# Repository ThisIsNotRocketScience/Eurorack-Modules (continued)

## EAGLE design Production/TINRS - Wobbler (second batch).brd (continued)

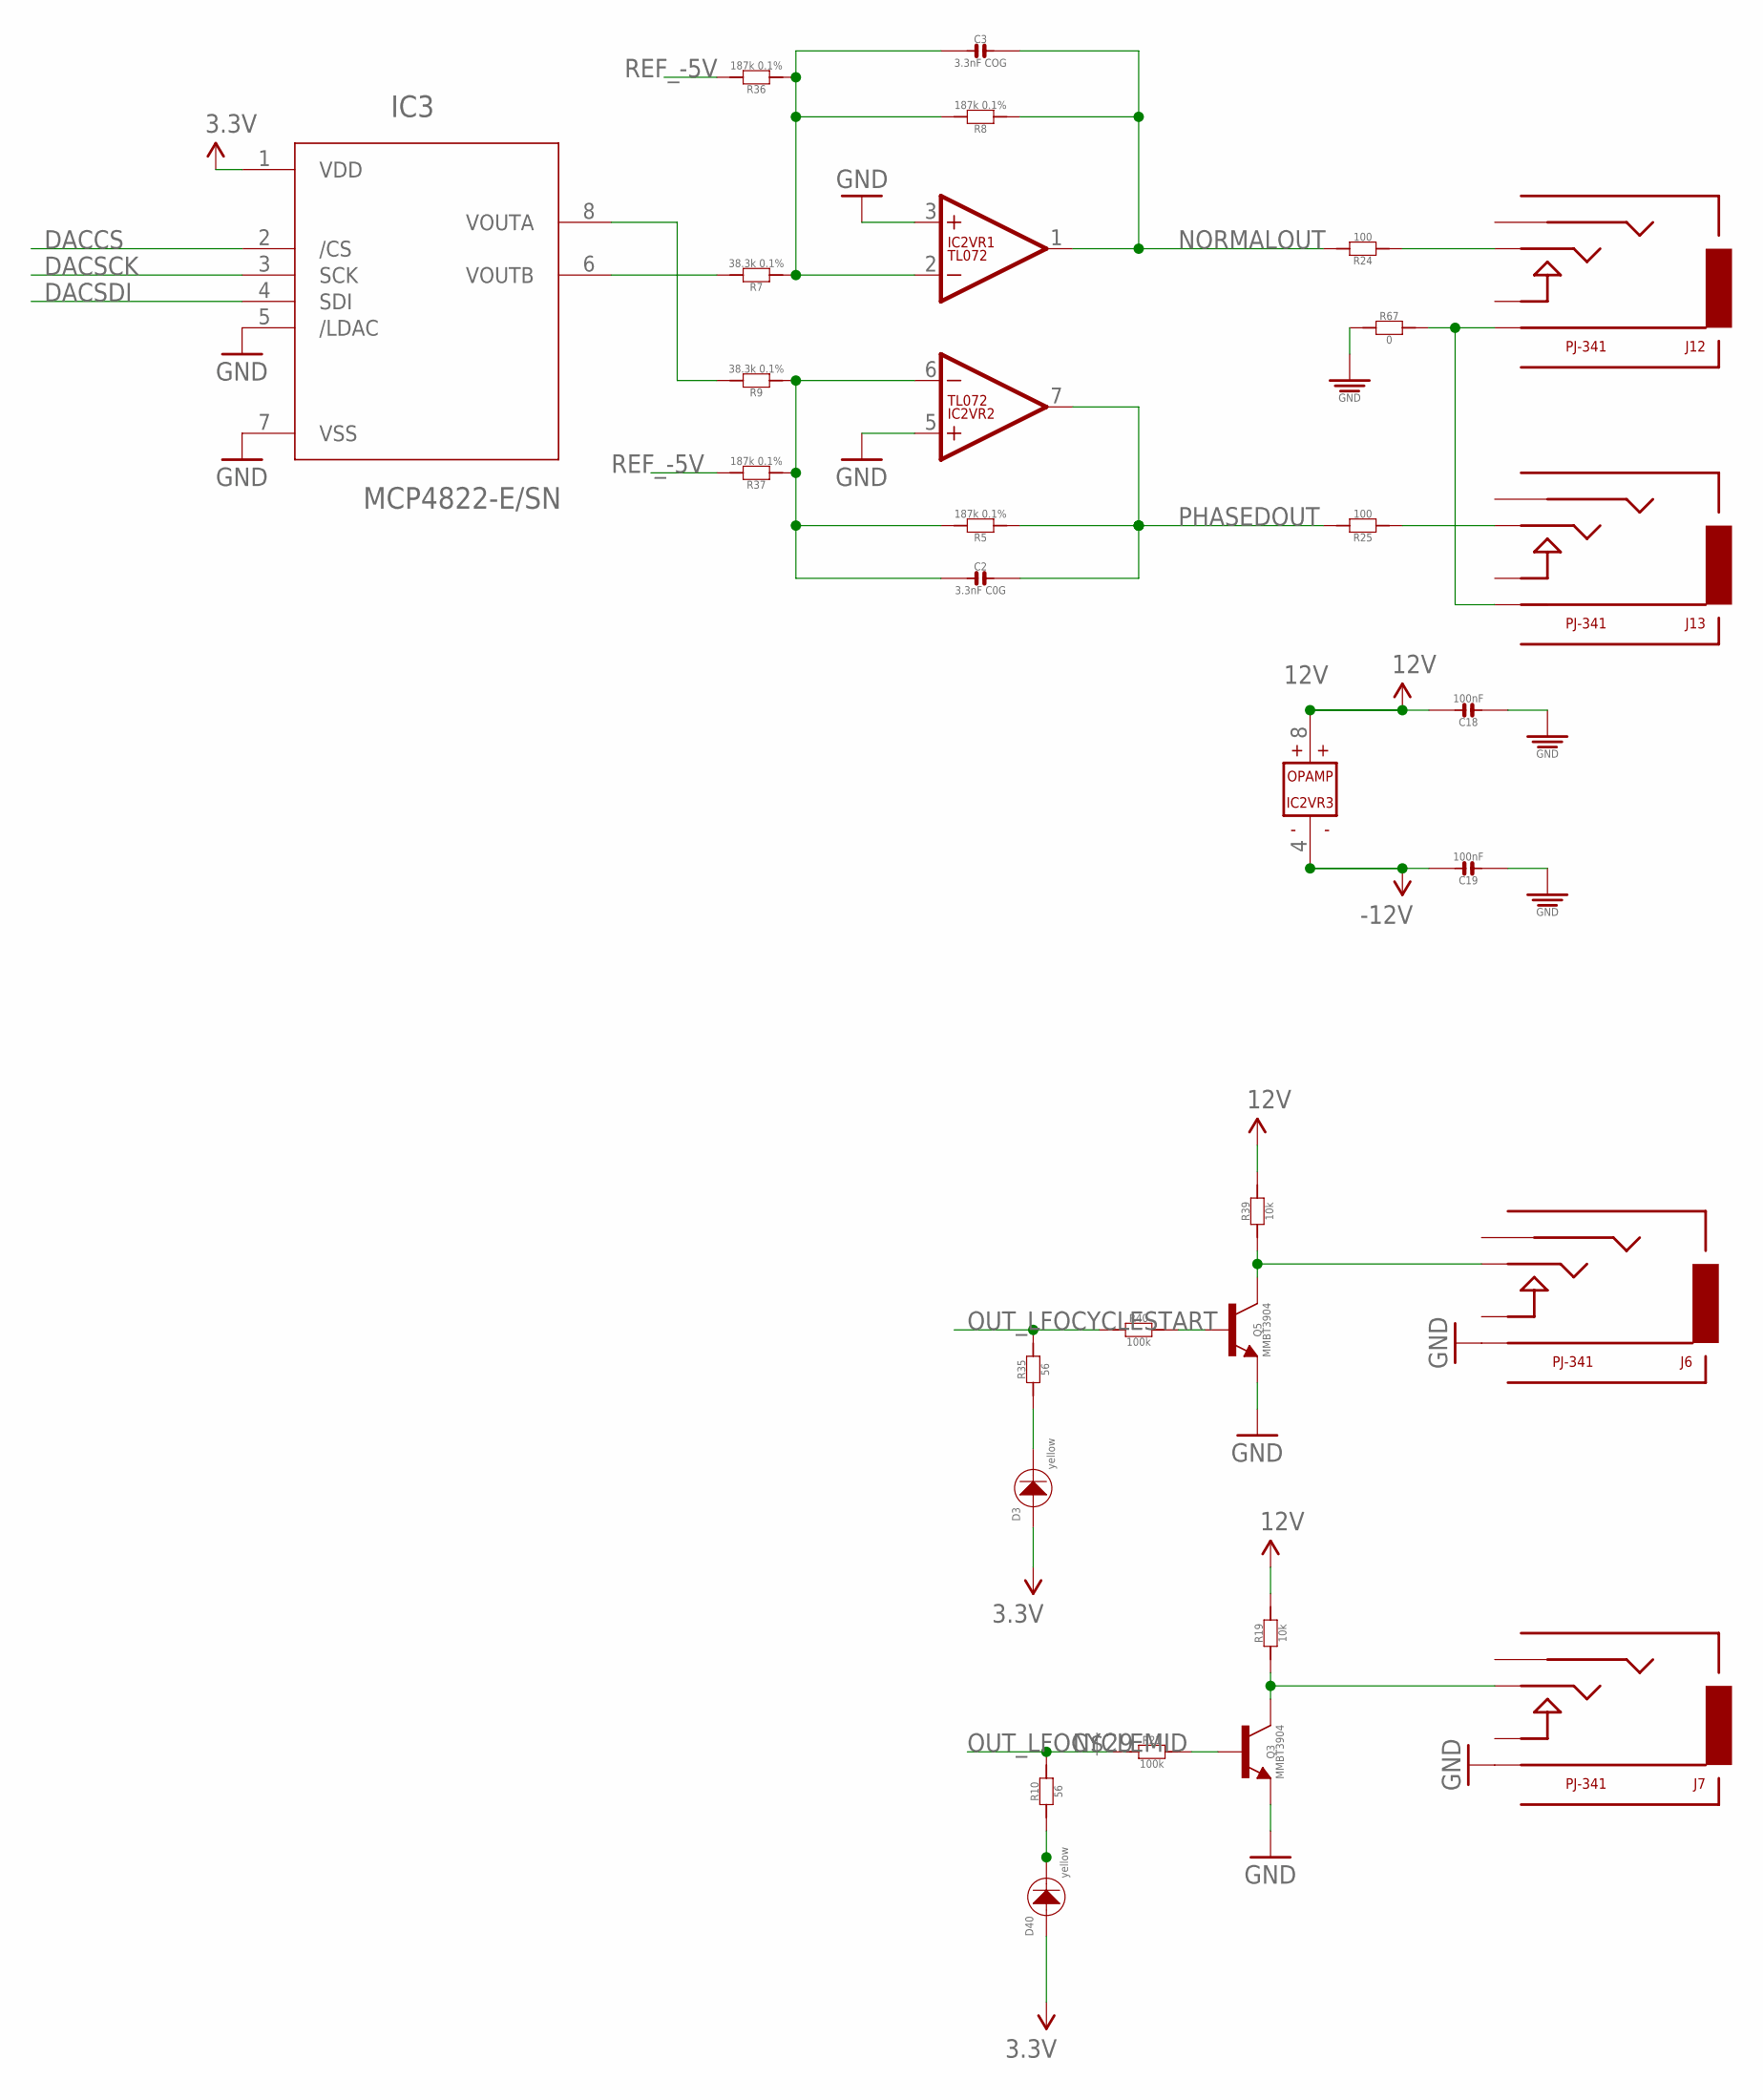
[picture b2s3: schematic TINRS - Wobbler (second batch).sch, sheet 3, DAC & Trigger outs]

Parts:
C2: 3.3nF C0G; C0603
C3: 3.3nF COG; C0603
C18, C19: 100nF; C0603; MPN MC0603F104Z160CT
D3, D40: yellow; 3MMLED
IC2: TL072; SO08
IC3: MCP4822-E/SN; SOIC8-N_MC
J6, J7, J12, J13: PJ-341; 3.5MM-JACK-SWITCH-13MM-OUTPUT
Q3, Q5: MMBT3904; SOT23-BEC; MPN PMBT3904,215
R5, R8, R36, R37: 187k 0.1%; R0603
R7, R9: 38.3k 0.1%; R0603
R10, R35: 56; R0603
R19, R39: 10k; R0603
R21, R40: 100k; R0603
R24, R25: 100; R0603
R67: 0; R0603

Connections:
3.3V: D3.+, D40.+, IC3.1 (VDD); also elsewhere on the board
12V: C18.2, IC2.8 (V+), R19.2, R39.2; also elsewhere on the board
-12V: C19.2, IC2.4 (V-); also elsewhere on the board
DACCS: IC3.2 (/CS); also elsewhere on the board
DACSCK: IC3.3 (SCK); also elsewhere on the board
DACSDI: IC3.4 (SDI); also elsewhere on the board
GND: C18.1, C19.1, IC2.3 (+IN), IC2.5 (+IN), IC3.5 (/LDAC), IC3.7 (VSS), J6.RING@3 (RING), J7.RING@3 (RING), Q3.E, Q5.E, R67.1; also elsewhere on the board
unnamed: IC3.8 (VOUTA), R9.2
unnamed: IC3.6 (VOUTB), R7.2
unnamed: C2.1, IC2.6 (-IN), R5.2, R9.1, R37.1
unnamed: C3.1, IC2.2 (-IN), R7.1, R8.2, R36.1
unnamed: J13.TIP@3 (TIP), R25.1
unnamed: J12.TIP@3 (TIP), R24.1
unnamed: D40.-, R10.1
unnamed: Q3.B, R21.2
unnamed: D3.-, R35.1
unnamed: J7.TIP@3 (TIP), Q3.C, R19.1
unnamed: Q5.B, R40.2
unnamed: J6.TIP@3 (TIP), Q5.C, R39.1
NORMALOUT: C3.2, IC2.1 (OUT), R8.1, R24.2
OUT_LFOCYCLEMID: R10.2, R21.1; also elsewhere on the board
OUT_LFOCYCLESTART: R35.2, R40.1; also elsewhere on the board
PHASEDOUT: C2.2, IC2.7 (OUT), R5.1, R25.2
REF_-5V: R36.2, R37.2; also elsewhere on the board
RETURNGROUND: J12.RING@3 (RING), J13.RING@3 (RING), R67.2

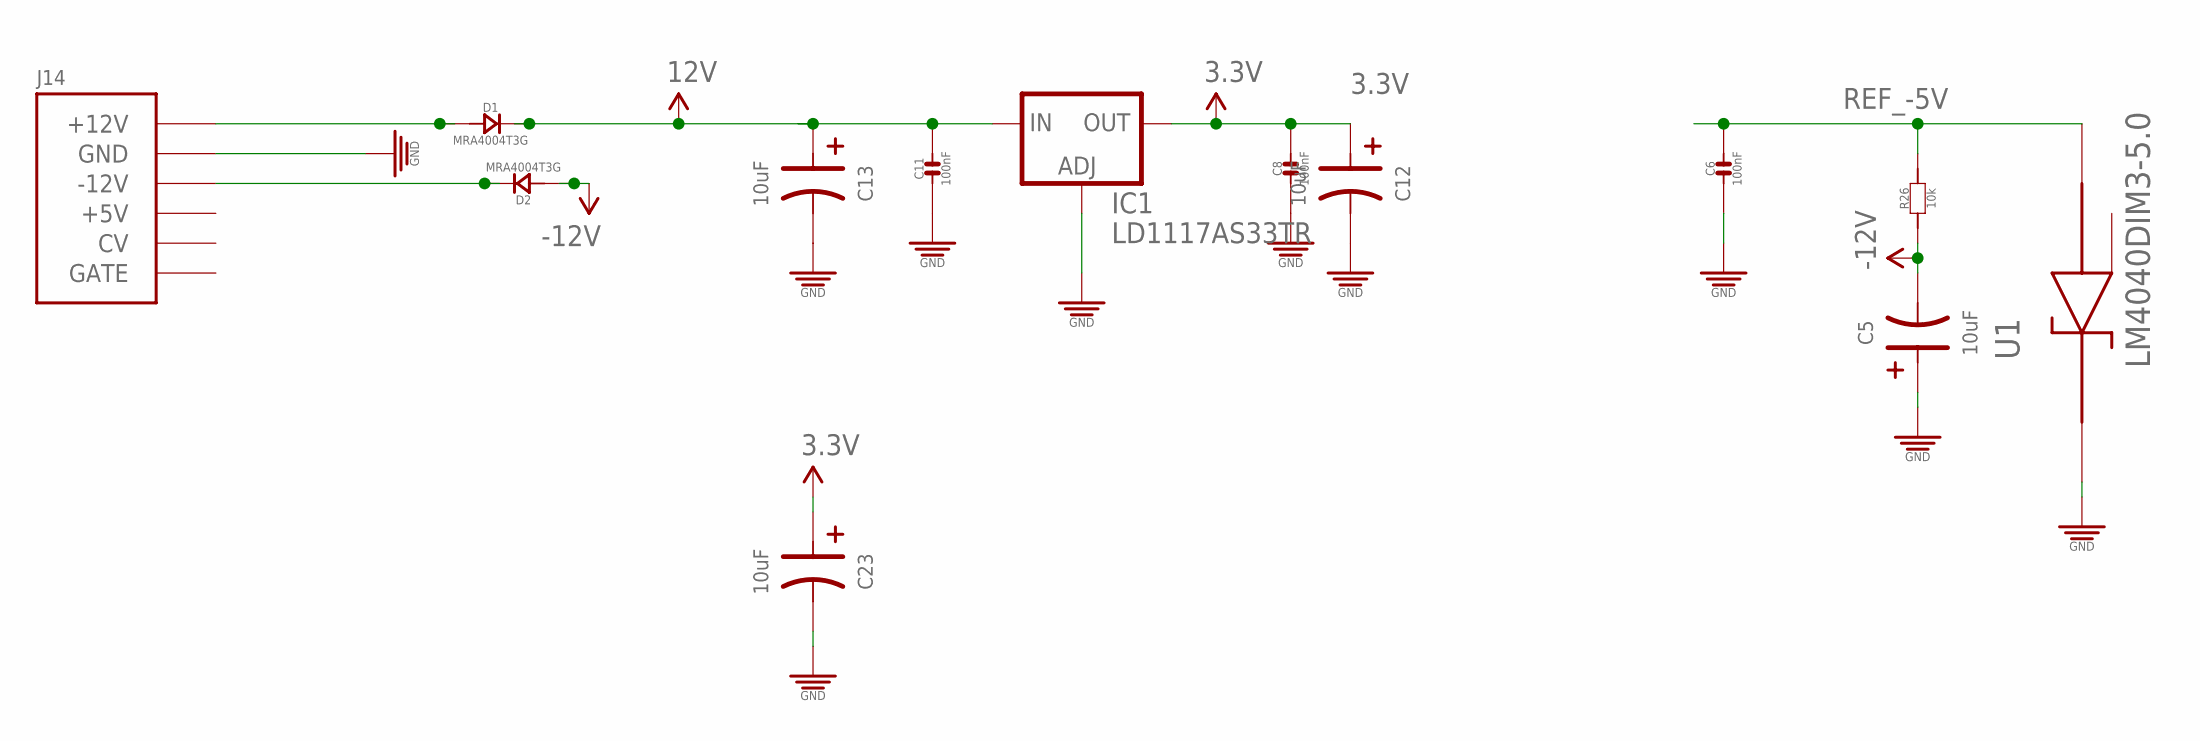
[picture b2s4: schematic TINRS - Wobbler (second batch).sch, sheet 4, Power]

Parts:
C5, C12, C13, C23: 10uF; CASE-A_3216; MPN TAJB106K020RNJ
C6: 100nF; C0603; MPN 06035C104KAT2A
C8, C11: 100nF; C0603; MPN MC0603F104Z160CT
D1, D2: MRA4004T3G; DO-214AC; MPN US1G-E3/5AT
IC1: LD1117AS33TR; SOT223; MPN LD1117AS33TR
J14: POWERSMT; 2X08_SMT_HEADER
R26: 10k; R0603
U1: LM4040DIM3-5.0; SOT95P237X112-3N

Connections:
3.3V: C8.2, C12.+ (1), C23.+ (1), IC1.2 (OUT), IC1.4 (OUT); also elsewhere on the board
12V: C11.2, C13.+ (1), D1.2 (-), IC1.3 (IN); also elsewhere on the board
-12V: C5.- (2), D2.1 (+), R26.1; also elsewhere on the board
GND: C5.+ (1), C6.1, C8.1, C11.1, C12.- (2), C13.- (2), C23.- (2), IC1.1 (ADJ), J14.3 (GND), J14.4 (GND), J14.5 (GND), J14.6 (GND), J14.7 (GND), J14.8 (GND), U1.1 (CATHODE); also elsewhere on the board
unnamed: D1.1 (+), J14.9 (+12V), J14.10 (+12V)
unnamed: D2.2 (-), J14.1 (-12V), J14.2 (-12V)
REF_-5V: C6.2, R26.2, U1.2 (ANODE); also elsewhere on the board

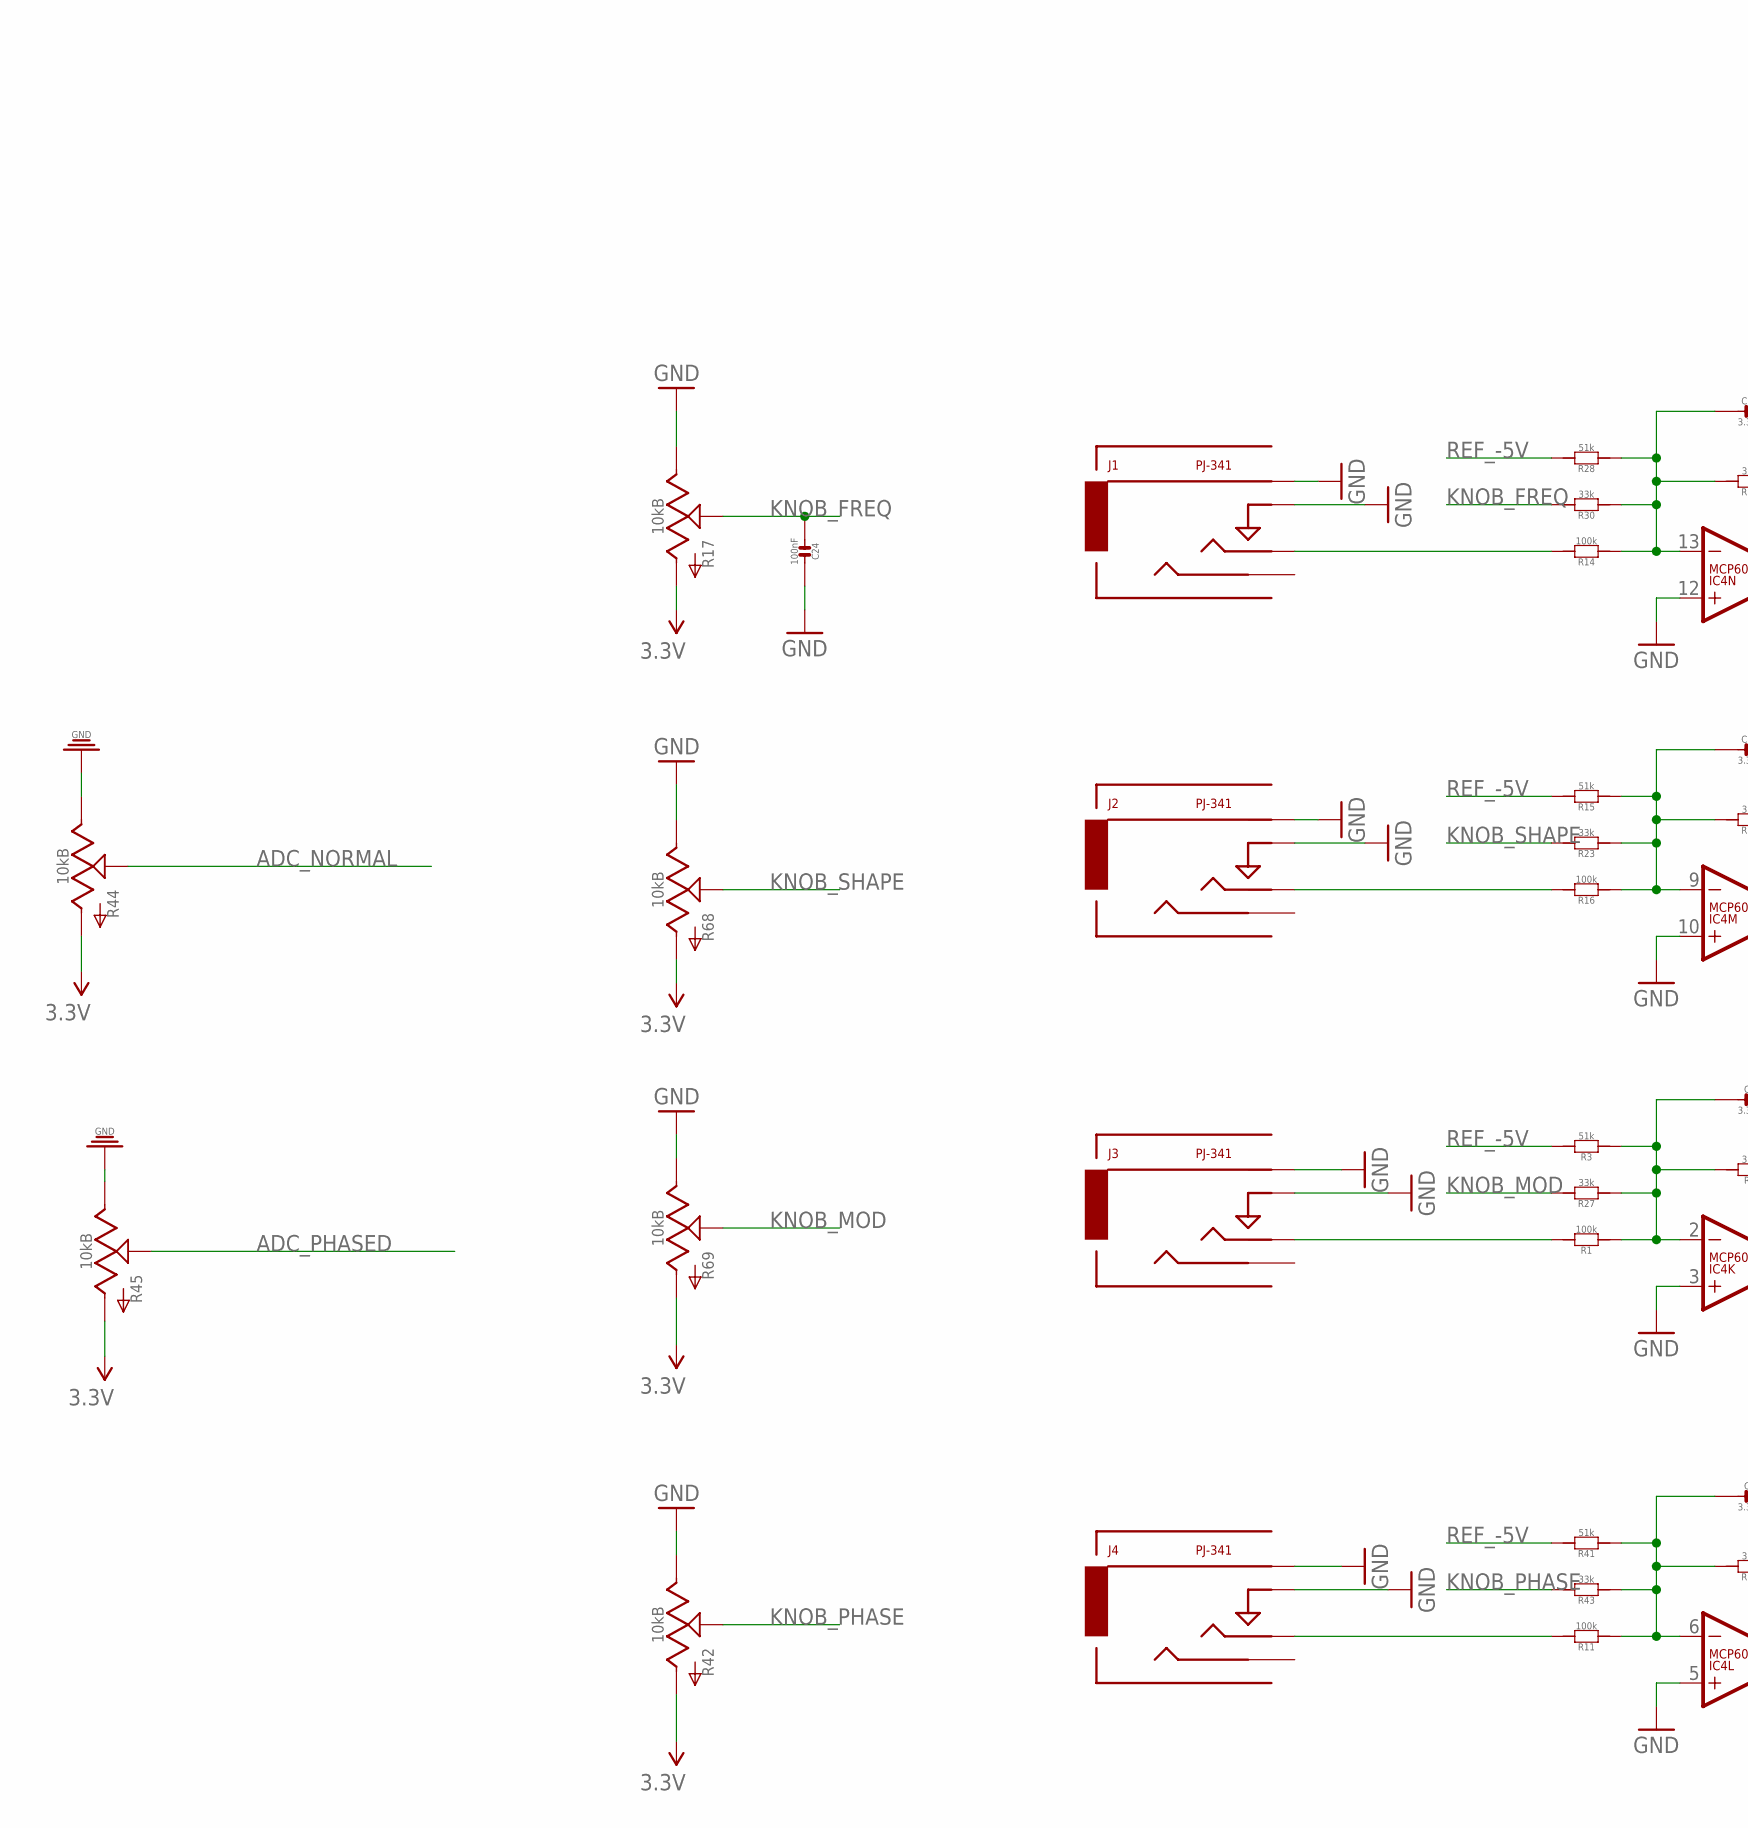
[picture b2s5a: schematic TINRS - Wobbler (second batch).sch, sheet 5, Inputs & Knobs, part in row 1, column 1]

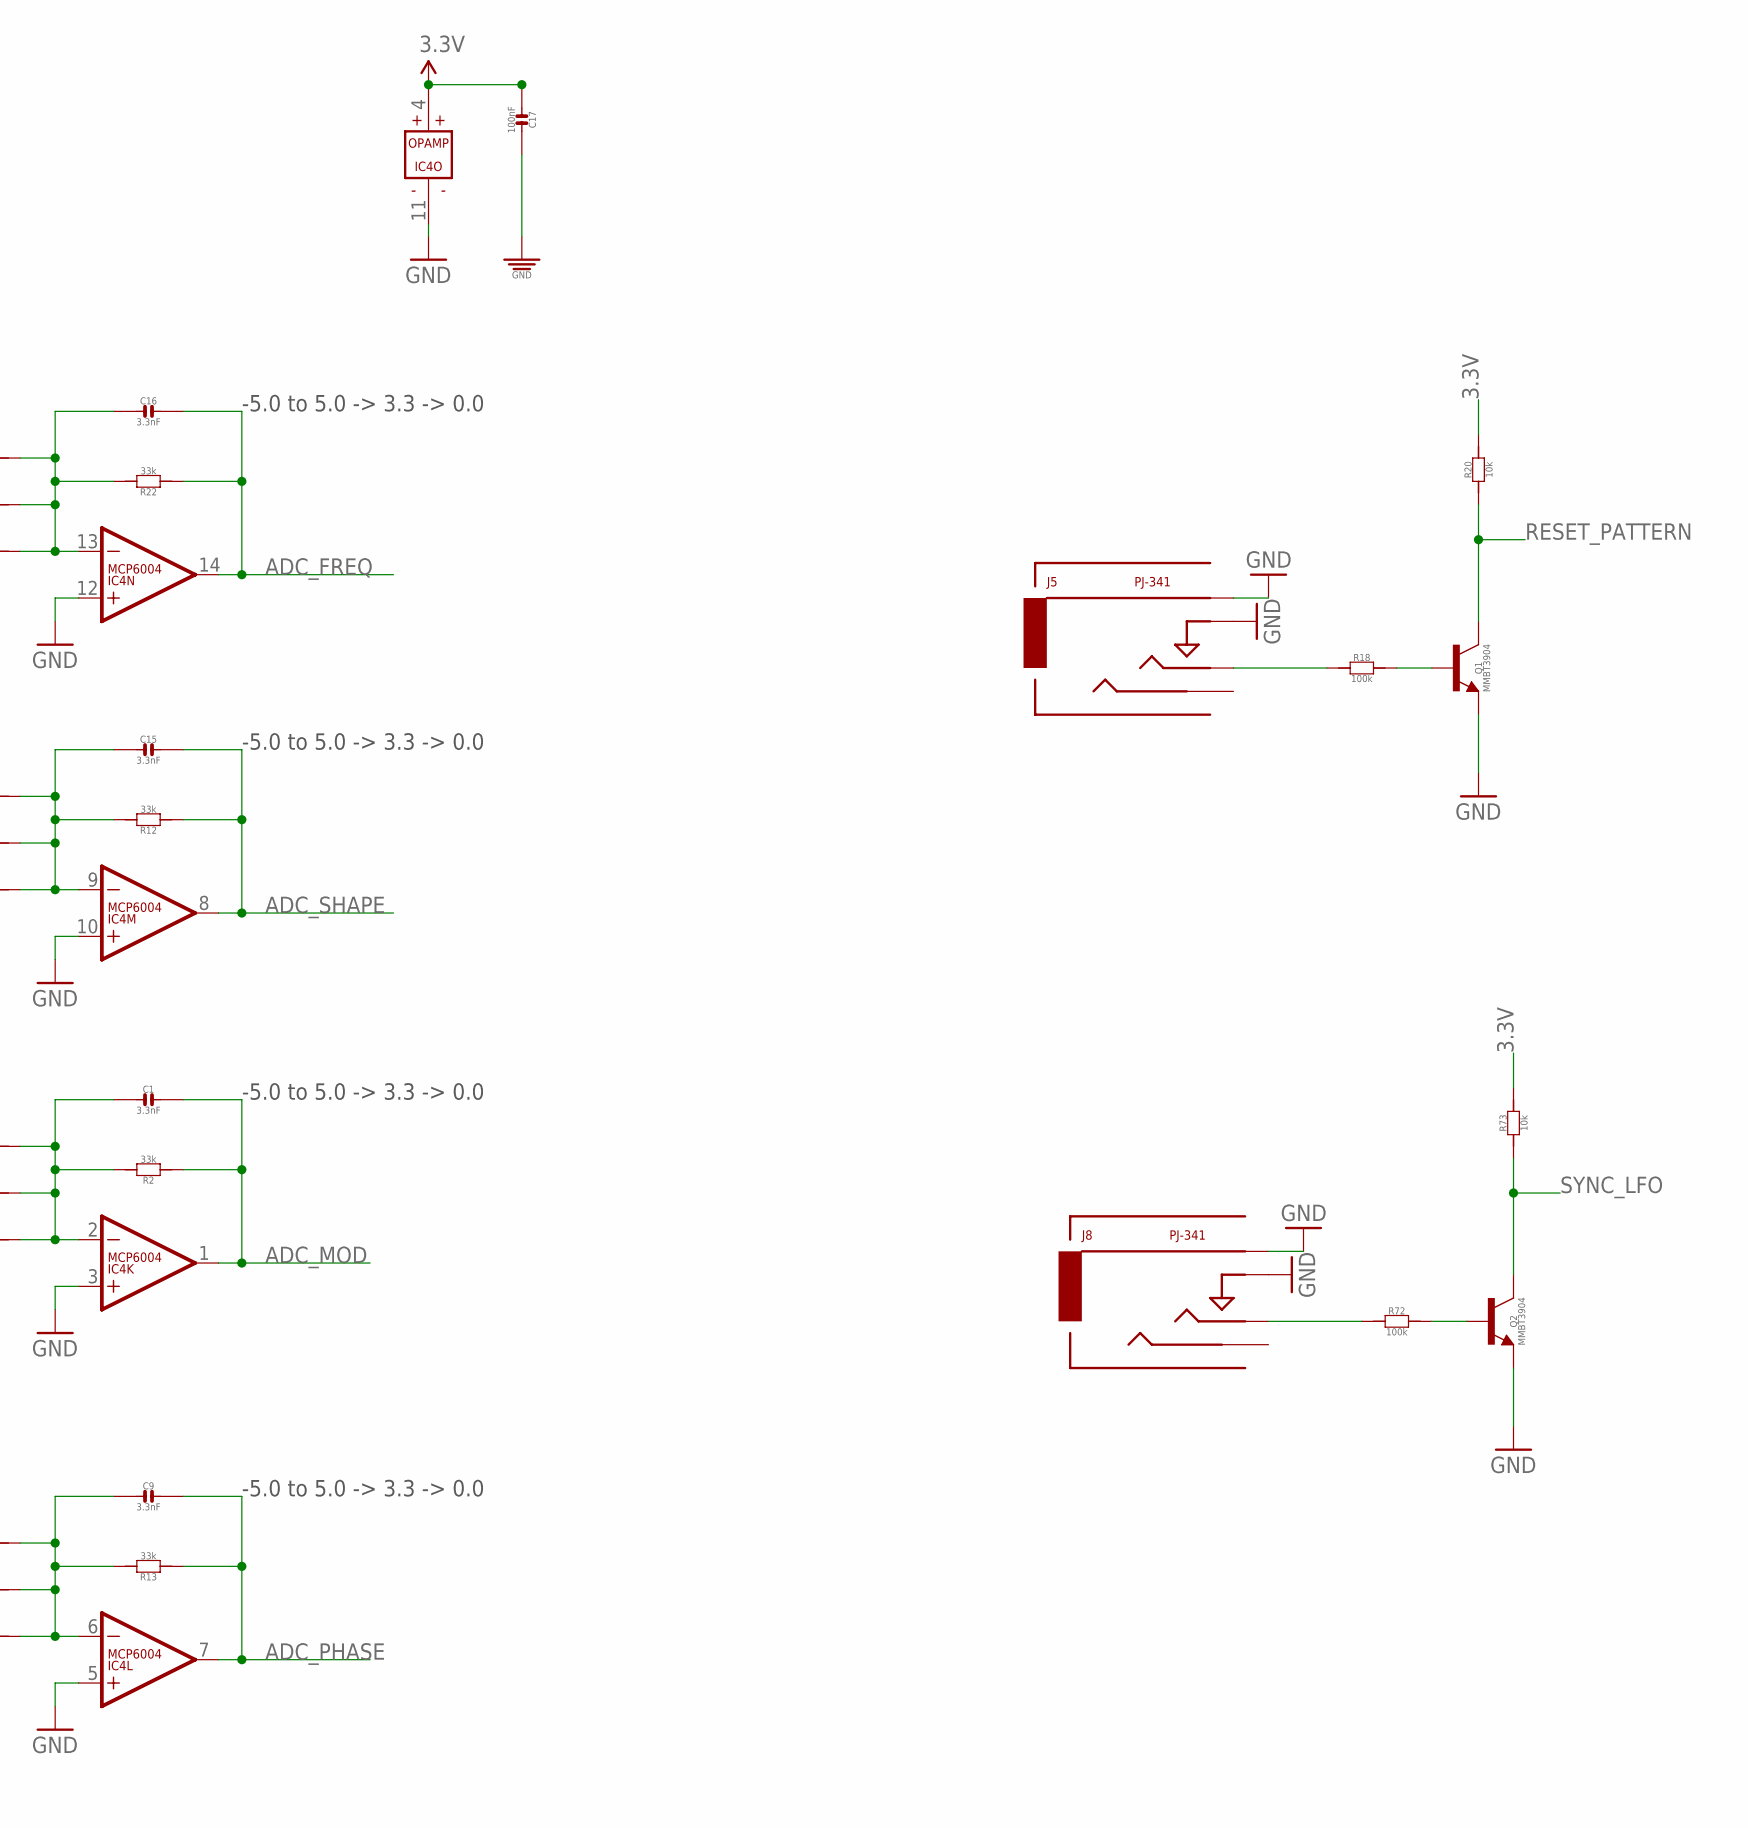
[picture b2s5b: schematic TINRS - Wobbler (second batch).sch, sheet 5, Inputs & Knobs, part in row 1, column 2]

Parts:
C1, C9, C15, C16: 3.3nF; C0603
C17, C24: 100nF; C0603; MPN MC0603F104Z160CT
IC4: MCP6004; SO14; MPN MCP6004-I/SL.
J1, J2, J3, J4, J5, J8: PJ-341; 3.5MM-JACK-SWITCH-13MM-INPUT
Q1, Q2: MMBT3904; SOT23-BEC; MPN PMBT3904,215
R1, R11, R14, R16, R18, R72: 100k; R0603
R2, R12, R13, R22, R23, R27, R30, R43: 33k; R0603
R3, R15, R28, R41: 51k; R0603
R17, R42, R44, R45, R68, R69: 10kB; ALPS_POT_SQUAREHOLES
R20, R73: 10k; R0603

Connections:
3.3V: C17.1, IC4.4 (V+), R17.P$3 (A), R20.2, R42.P$3 (A), R44.P$3 (A), R45.P$3 (A), R68.P$3 (A), R69.P$3 (A), R73.2; also elsewhere on the board
ADC_FREQ: C16.2, IC4.14 (OUT), R22.1; also elsewhere on the board
ADC_MOD: C1.2, IC4.1 (OUT), R2.1; also elsewhere on the board
ADC_NORMAL: R44.P$2 (S); also elsewhere on the board
ADC_PHASE: C9.2, IC4.7 (OUT), R13.1; also elsewhere on the board
ADC_PHASED: R45.P$2 (S); also elsewhere on the board
ADC_SHAPE: C15.2, IC4.8 (OUT), R12.1; also elsewhere on the board
GND: C17.2, C24.2, IC4.3 (+IN), IC4.5 (+IN), IC4.10 (+IN), IC4.11 (V-), IC4.12 (+IN), J1.RING@3 (RING), J1.SWITCH@3 (SWITCH), J2.RING@3 (RING), J2.SWITCH@3 (SWITCH), J3.RING@3 (RING), J3.SWITCH@3 (SWITCH), J4.RING@3 (RING), J4.SWITCH@3 (SWITCH), J5.RING@3 (RING), J5.SWITCH@3 (SWITCH), J8.RING@3 (RING), J8.SWITCH@3 (SWITCH), Q1.E, Q2.E, R17.P$1 (E), R42.P$1 (E), R44.P$1 (E), R45.P$1 (E), R68.P$1 (E), R69.P$1 (E); also elsewhere on the board
KNOB_FREQ: C24.1, R17.P$2 (S), R30.2
KNOB_MOD: R27.2, R69.P$2 (S)
KNOB_PHASE: R42.P$2 (S), R43.2
KNOB_SHAPE: R23.2, R68.P$2 (S)
unnamed: J2.TIP@3 (TIP), R16.2
unnamed: C15.1, IC4.9 (-IN), R12.2, R15.1, R16.1, R23.1
unnamed: J3.TIP@3 (TIP), R1.2
unnamed: C1.1, IC4.2 (-IN), R1.1, R2.2, R3.1, R27.1
unnamed: J4.TIP@3 (TIP), R11.2
unnamed: C9.1, IC4.6 (-IN), R11.1, R13.2, R41.1, R43.1
unnamed: Q1.B, R18.2
unnamed: J5.TIP@3 (TIP), R18.1
unnamed: J1.TIP@3 (TIP), R14.2
unnamed: C16.1, IC4.13 (-IN), R14.1, R22.2, R28.1, R30.1
unnamed: Q2.B, R72.2
unnamed: J8.TIP@3 (TIP), R72.1
REF_-5V: R3.2, R15.2, R28.2, R41.2; also elsewhere on the board
RESET_PATTERN: Q1.C, R20.1; also elsewhere on the board
SYNC_LFO: Q2.C, R73.1; also elsewhere on the board

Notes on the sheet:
-5.0 to 5.0 -> 3.3 -> 0.0

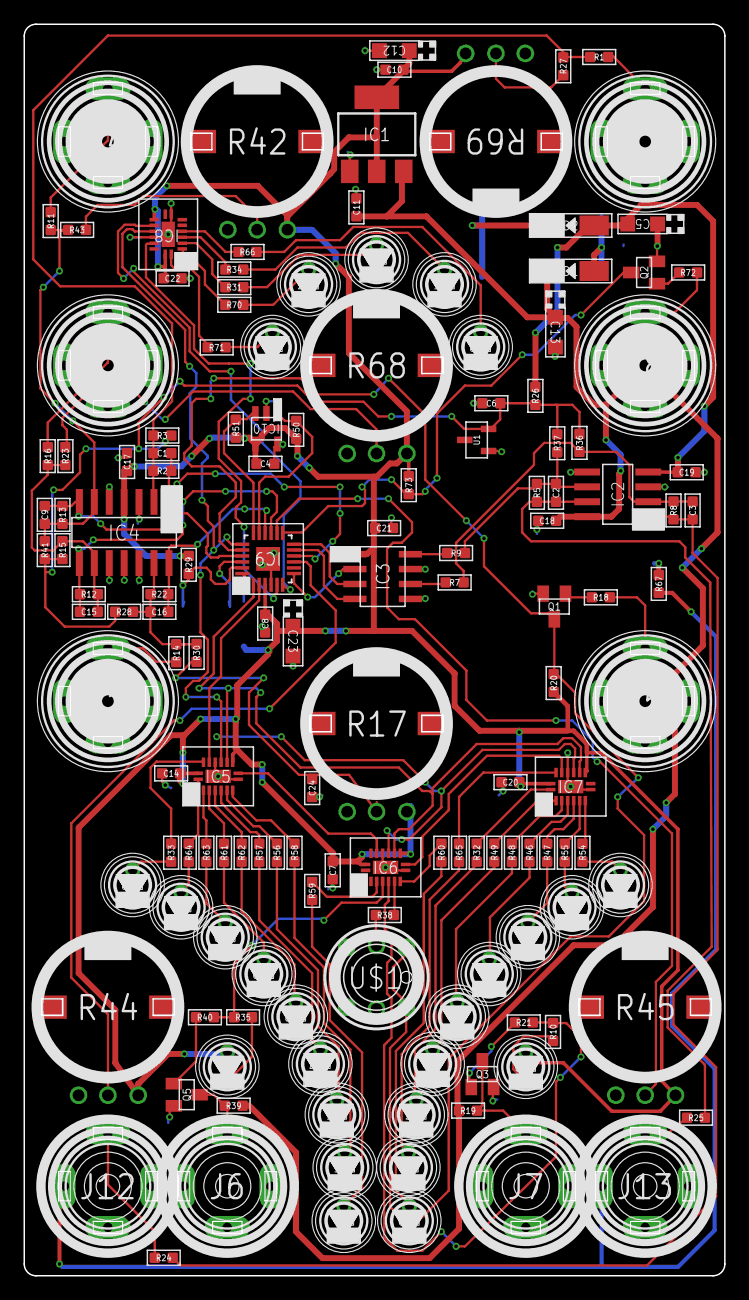
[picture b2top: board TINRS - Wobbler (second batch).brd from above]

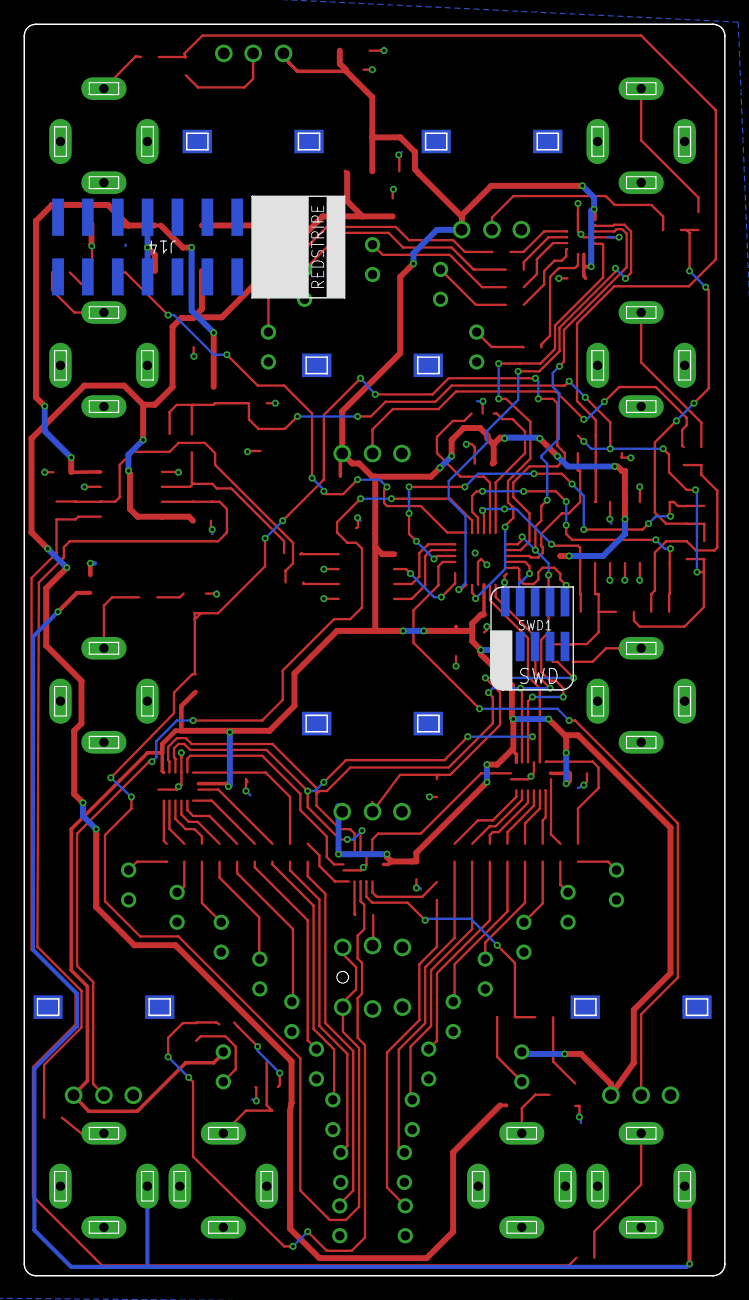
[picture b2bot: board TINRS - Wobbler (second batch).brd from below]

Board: 2 copper layers, 59.6 x 106.5 mm, 149 parts (2 on the bottom side), 111 nets.
